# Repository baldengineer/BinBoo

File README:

This project is my first attempt to commit to GitHub.  The hardware files are for the PCB used on the controller board.  It was created in a hurry and came back with many mistakes.  All mistakes have been corrected on the schematic but the PCB needs more work.

The code is as commented as I can make it.

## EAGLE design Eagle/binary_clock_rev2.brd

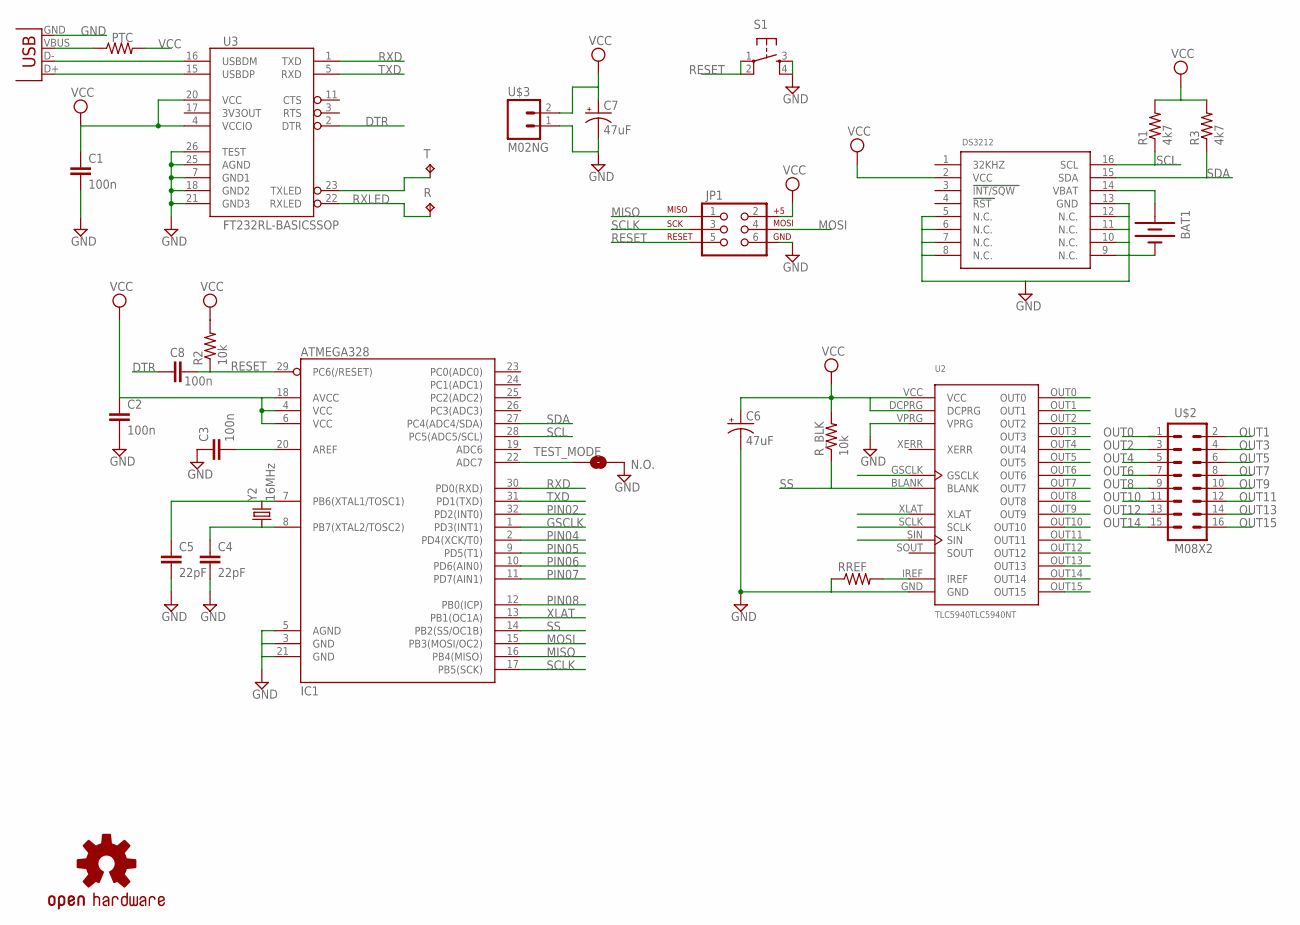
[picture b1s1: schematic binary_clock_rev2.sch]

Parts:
BAT1: BATTERY12MM; BATTCON_12MM
C1, C2, C3, C8: 100n; 1206
C4, C5: 22pF; 1206
C6, C7: 47uF; D/7343-31W
DS3212: DS3231; SO16L
IC1: ATMEGA328; TQFP32-08
JP1: AVR_SPI_PRG_62X3_LOCK; 2X3_LOCK
PTC: RESISTOR1206; 1206
R: TPB1,27; B1,27
R1, R3: 4k7; 1206
R2: 10k; 1206
RREF: 2.2k; 1206
R_BLK: 10k; 1206
S1: TAC_SWITCHSMD; TACTILE_SWITCH_SMD
T: TPB1,27; B1,27
TEST_MODE: N.O.; SJ_2S-NO
U2: TLC5940TLC5940NT; DIL28-3
U3: FT232RL-BASICSSOP; SSOP28DB
U$1: OSHW-LOGOM; OSHW-LOGO-M
U$2: M08X2; 2X8
U$3: M02NG; 1X02
X1: USBSMD; USB-MINIB
Y2: 16MHz; HC49US

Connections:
DTR: C8.1, U3.2 (DTR)
GND: BAT1.GND (-), C1.2, C2.2, C3.1, C4.2, C5.2, C6.-, C7.-, DS3212.5 (N.C.), DS3212.6 (N.C.), DS3212.7 (N.C.), DS3212.8 (N.C.), DS3212.9 (N.C.), DS3212.10 (N.C.), DS3212.11 (N.C.), DS3212.12 (N.C.), DS3212.13 (GND), IC1.3 (GND), IC1.5 (AGND), IC1.21 (GND), JP1.6, RREF.1, S1.3, S1.4, TEST_MODE.2, U2.GND, U2.VPRG, U3.7 (GND1), U3.18 (GND2), U3.21 (GND3), U3.25 (AGND), U3.26 (TEST), U$3.1, X1.GND
GSCLK: IC1.1 (PD3(INT1)), U2.GSCLK
MISO: IC1.16 (PB4(MISO)), JP1.1
MOSI: IC1.15 (PB3(MOSI/OC2)), JP1.4, U2.SIN
unnamed: IC1.22 (ADC7), TEST_MODE.1
unnamed: BAT1.PWR@2 (+), DS3212.14 (VBAT)
unnamed: U3.15 (USBDP), X1.D+
unnamed: U3.16 (USBDM), X1.D-
unnamed: C3.2, IC1.20 (AREF)
unnamed: PTC.1, X1.VBUS
unnamed: RREF.2, U2.IREF
unnamed: C5.1, IC1.7 (PB6(XTAL1/TOSC1)), Y2.2
unnamed: C4.1, IC1.8 (PB7(XTAL2/TOSC2)), Y2.1
OUT0: U2.OUT0, U$2.1
OUT1: U2.OUT1, U$2.2
OUT2: U2.OUT2, U$2.3
OUT3: U2.OUT3, U$2.4
OUT4: U2.OUT4, U$2.5
OUT5: U2.OUT5, U$2.6
OUT6: U2.OUT6, U$2.7
OUT7: U2.OUT7, U$2.8
OUT8: U2.OUT8, U$2.9
OUT9: U2.OUT9, U$2.10
OUT10: U2.OUT10, U$2.11
OUT11: U2.OUT11, U$2.12
OUT12: U2.OUT12, U$2.13
OUT13: U2.OUT13, U$2.14
OUT14: U2.OUT14, U$2.15
OUT15: U2.OUT15, U$2.16
PIN02: IC1.32 (PD2(INT0))
PIN04: IC1.2 (PD4(XCK/T0))
PIN05: IC1.9 (PD5(T1))
PIN06: IC1.10 (PD6(AIN0))
PIN07: IC1.11 (PD7(AIN1))
PIN08: IC1.12 (PB0(ICP))
RESET: C8.2, IC1.29 (PC6(/RESET)), JP1.5, R2.1, S1.1, S1.2
RXD: IC1.30 (PD0(RXD)), U3.1 (TXD)
RXLED: R.TP, U3.22 (RXLED)
SCL: DS3212.16 (SCL), IC1.28 (PC5(ADC5/SCL)), R1.1
SCLK: IC1.17 (PB5(SCK)), JP1.3, U2.SCLK
SDA: DS3212.15 (SDA), IC1.27 (PC4(ADC4/SDA)), R3.1
SS: IC1.14 (PB2(SS/OC1B)), R_BLK.1, U2.BLANK
TXD: IC1.31 (PD1(TXD)), U3.5 (RXD)
TXLED: T.TP, U3.23 (TXLED)
VCC: C1.1, C2.1, C6.+, C7.+, DS3212.2 (VCC), IC1.4 (VCC), IC1.6 (VCC), IC1.18 (AVCC), JP1.2, PTC.2, R1.2, R2.2, R3.2, R_BLK.2, U2.DCPRG, U2.VCC, U3.4 (VCCIO), U3.20 (VCC), U$3.2
XLAT: IC1.13 (PB1(OC1A)), U2.XLAT

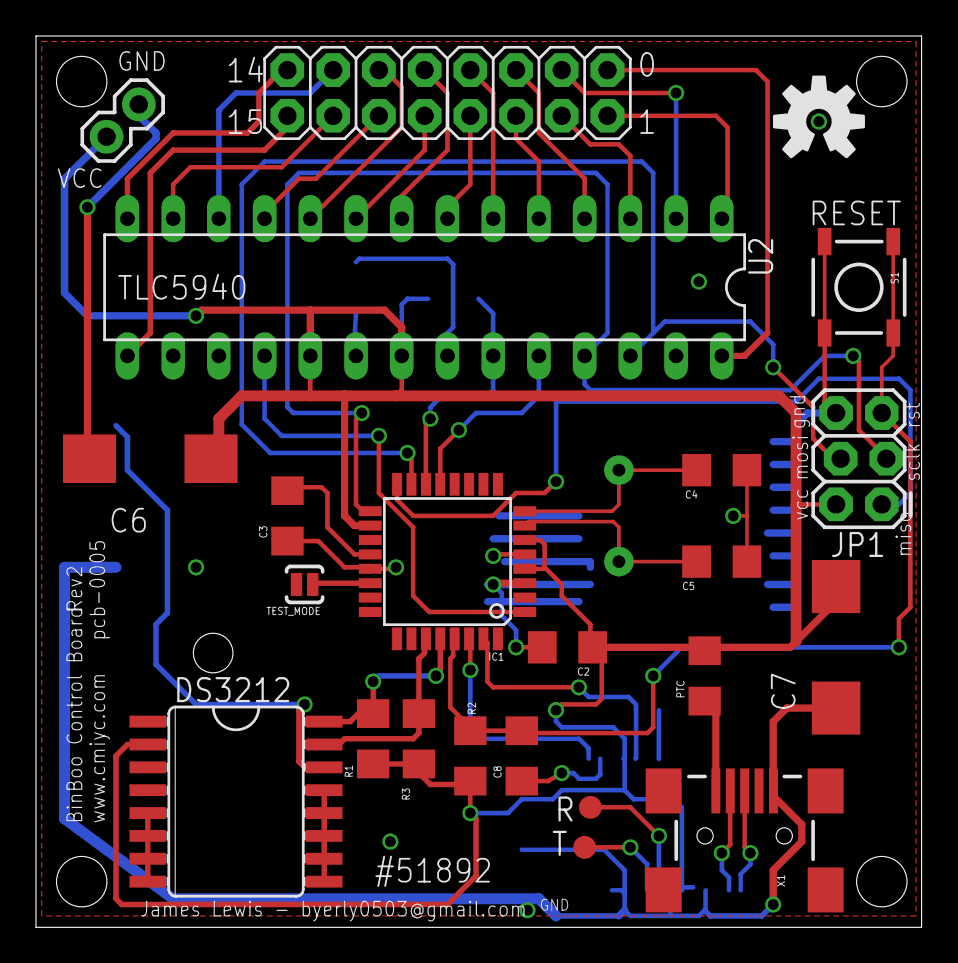
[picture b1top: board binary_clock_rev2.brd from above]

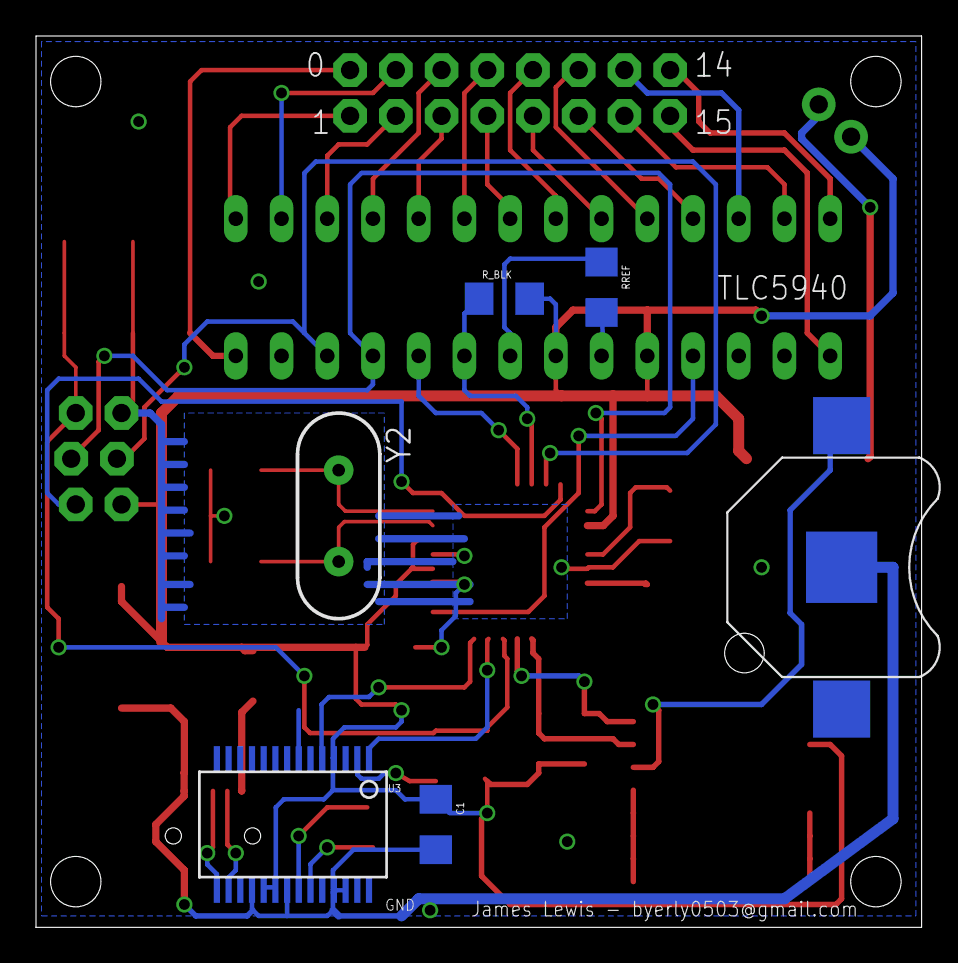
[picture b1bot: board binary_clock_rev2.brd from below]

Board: 2 copper layers, 49.2 x 49.5 mm, 29 parts (6 on the bottom side), 41 nets.

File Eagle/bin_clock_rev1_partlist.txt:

Partlist

Exported from binary_clock_rev1.sch at 10/12/11 9:47 PM

EAGLE Version 5.11.0 Copyright (c) 1988-2010 CadSoft

Part     Value             Device                Package            Library   Sheet

BAT1                       BATTERY12MM           BATTCON_12MM       SparkFun  1
C1       100n              CAP1206               1206               SparkFun  1
C2       100n              CAP1206               1206               SparkFun  1
C3       100n              CAP1206               1206               SparkFun  1
C4       22pF              CAP1206               1206               JitterLab 1
C5       22pF              CAP1206               1206               JitterLab 1
C6       47uF              CPOL-USD/7343-31W     D/7343-31W         rcl       1
C7       47uF              CPOL-USD/7343-31W     D/7343-31W         rcl       1
IC1      ATMEGA168         ATMEGA168             TQFP32-08          SparkFun  1
JP1                        AVR_SPI_PRG_62X3_LOCK 2X3_LOCK           SparkFun  1
PTC                        RESISTOR1206          1206               SparkFun  1
R        TPB1,27           TPB1,27               B1,27              testpad   1
R1       4K7               RESISTOR1206          1206               JitterLab 1
R2       10k               RESISTOR1206          1206               SparkFun  1
R3       4k7               RESISTOR1206          1206               JitterLab 1
RREF     2.2k              RESISTOR1206          1206               JitterLab 1
R_BLK    10k               RESISTOR1206          1206               JitterLab 1
S1                         TAC_SWITCHSMD         TACTILE_SWITCH_SMD SparkFun  1
T        TPB1,27           TPB1,27               B1,27              testpad   1
U$1      DS1307SO8         DS1307SO8             SO08               SparkFun  1
U$2      M08X2             M08X2                 2X8                SparkFun  1
U$3      M04X2             M04X2                 2X4                SparkFun  1
U2       TLC5940TLC5940NT  TLC5940TLC5940NT      DIL28-3            TLC5940NT 1
U3       FT232RL-BASICSSOP FT232RL-BASICSSOP     SSOP28DB           SparkFun  1
X1       USBSMD            USBSMD                USB-MINIB          SparkFun  1
Y1       32kHz             CRYSTAL32-SMD         CRYSTAL-32KHZ-SMD  SparkFun  1
Y2       16MHz             CRYSTALHC49US         HC49US             SparkFun  1

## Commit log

2011-10-29 Initial Commit
    Each direction contains the appropriate files for either the firmware,
    the pcb, or the enclosure.
2011-10-30 Schematic Fixes and First Code Commit
    Schematic needed significant changes. The FTDI isn't wired correctly,
    nor is the TLC5940. The TLC has missing VCC/GND connections. More
    problematic is that the "GND" bar for the LEDs is completely wrong.
    The TLC sinks current, not sources it (duh).
2011-10-30 git ignore?
2011-10-30 why?
2011-11-05 Smooth fading for time changes.
    Added some code to smoothly fade the LEDs on/off as the time changes.
    Subtle effect but takes away from the stark "on" then "off."
2011-11-27 Major box update
    None of the pieces from rev1 work. This is a completely re-worked
    version. All pieces that are cut by ponoko have been turned into
    Components in Google Sketchup.
2011-11-27 Why can't I ignore these?
2012-05-27 BCD Version of the code
    This code now expected 4 columns with 4 LEDs to represent a BCD of the
    time.
2012-05-27 Huh?
2012-05-29 Replaced DS1307 with a DS3212 and other fixes.
    Schematic Changes:
    * Added solderable-jumper (n.o.) on ATmega328, ADC7 to enable "test
    mode"
    * Fixed errors on FT232R:
    * tied reset to VCC (on PCB only)
    * Swapped TX and RX (so that they are crossed going into
